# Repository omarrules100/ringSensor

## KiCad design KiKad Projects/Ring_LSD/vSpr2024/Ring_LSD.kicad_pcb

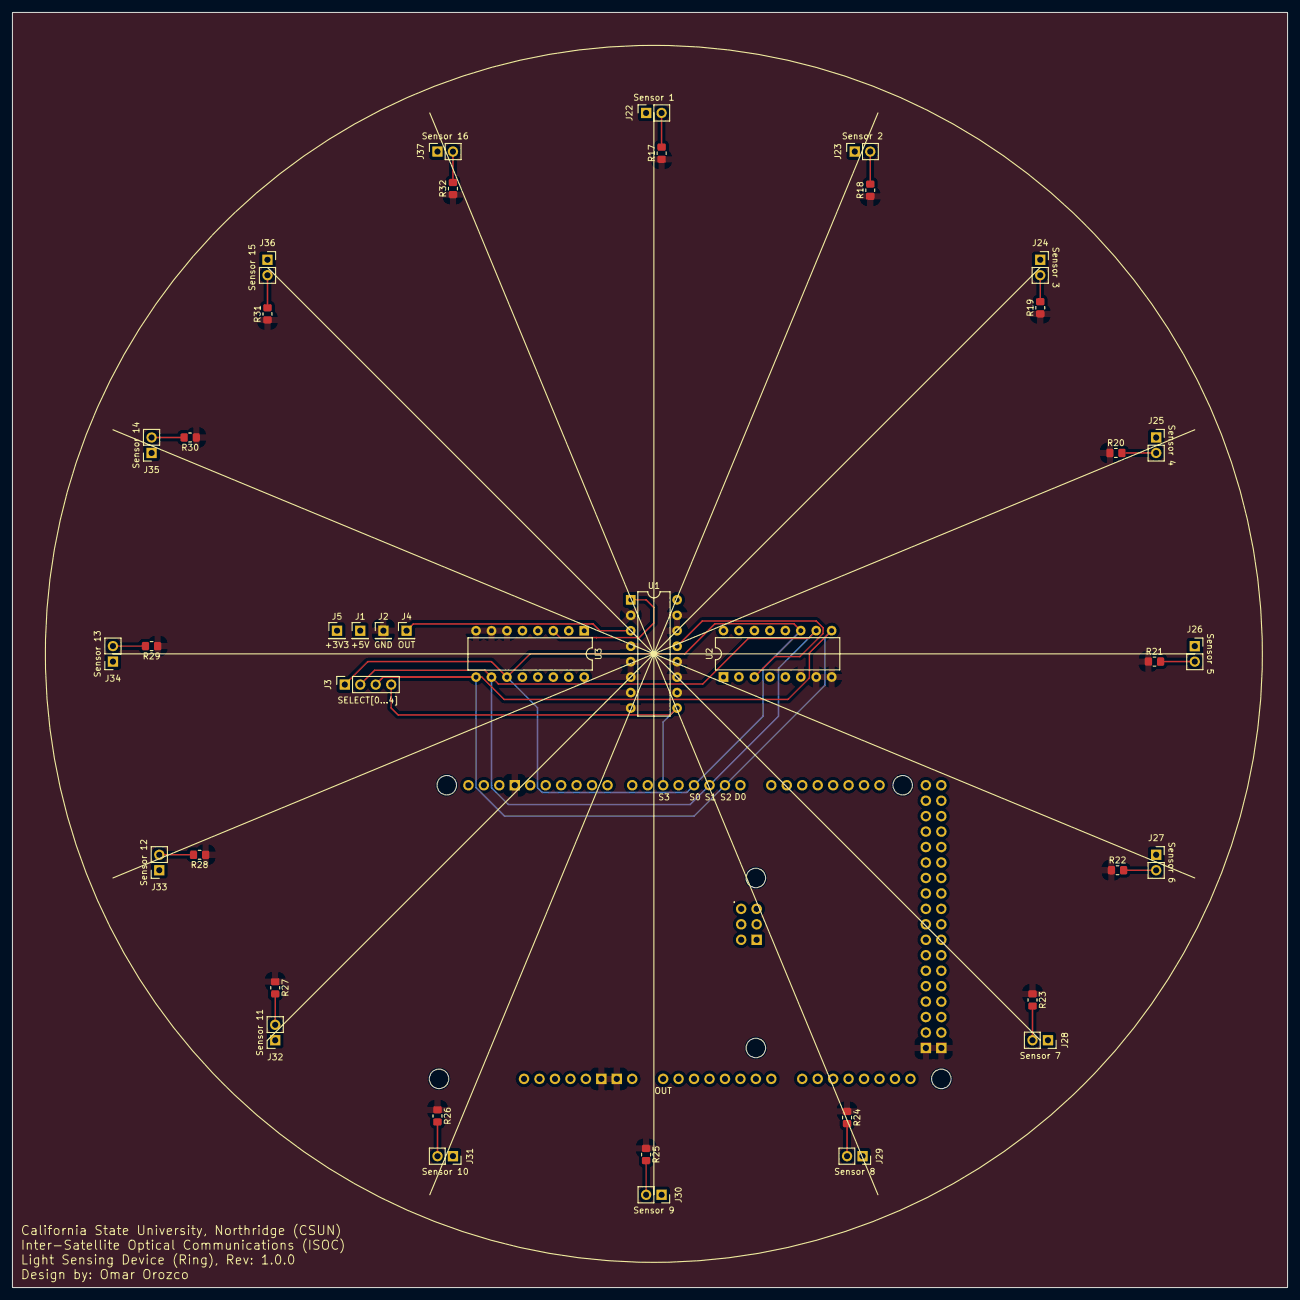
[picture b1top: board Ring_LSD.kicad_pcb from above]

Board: 4 copper layers, 209.5 x 209.5 mm, 41 parts (0 on the bottom side), 26 nets.

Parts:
A1: Arduino_Giga_R1_WiFi_Shield
J1: +5V; PinHeader_1x01_P2.54mm_Vertical
J2: GND; PinHeader_1x01_P2.54mm_Vertical
J3: SELECT[0...4]; PinSocket_1x04_P2.54mm_Vertical
J4: OUT; PinHeader_1x01_P2.54mm_Vertical
J5: +3V3; PinHeader_1x01_P2.54mm_Vertical
J22: Sensor 1; PinSocket_1x02_P2.54mm_Vertical
J23: Sensor 2; PinSocket_1x02_P2.54mm_Vertical
J24: Sensor 3; PinSocket_1x02_P2.54mm_Vertical
J25: Sensor 4; PinSocket_1x02_P2.54mm_Vertical
J26: Sensor 5; PinSocket_1x02_P2.54mm_Vertical
J27: Sensor 6; PinSocket_1x02_P2.54mm_Vertical
J28: Sensor 7; PinSocket_1x02_P2.54mm_Vertical
J29: Sensor 8; PinSocket_1x02_P2.54mm_Vertical
J30: Sensor 9; PinSocket_1x02_P2.54mm_Vertical
J31: Sensor 10; PinSocket_1x02_P2.54mm_Vertical
J32: Sensor 11; PinSocket_1x02_P2.54mm_Vertical
J33: Sensor 12; PinSocket_1x02_P2.54mm_Vertical
J34: Sensor 13; PinSocket_1x02_P2.54mm_Vertical
J35: Sensor 14; PinSocket_1x02_P2.54mm_Vertical
J36: Sensor 15; PinSocket_1x02_P2.54mm_Vertical
J37: Sensor 16; PinSocket_1x02_P2.54mm_Vertical
R17, R18, R19, R20, R21, R22, R23, R24, R25, R26, R27, R28, R29, R30, R31, R32: 5K; R_0805_2012Metric_Pad1.20x1.40mm_HandSolder
U1, U2, U3: 74HCT4051; DIP-16_W7.62mm

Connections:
+3V3: J5.1, J22.1, J23.1, J24.1, J25.1, J26.1, J27.1, J28.1, J29.1, J30.1, J31.1, J32.1, J33.1, J34.1, J35.1, J36.1, J37.1
+5V: J1.1, U1.16 (VCC), U2.16 (VCC), U3.16 (VCC)
/LSD_OUT: A1.A0, J4.1, U1.3 (Z)
/Select0: A1.D3, J3.1, U2.11 (S0), U3.11 (S0)
/Select1: A1.D2, J3.2, U2.10 (S1), U3.10 (S1)
/Select2: A1.D1 (D1/TX0), J3.3, U2.9 (S2), U3.9 (S2)
/Select3: A1.D5, J3.4, U1.9 (S2)
/Z1: U1.13 (Y0), U2.3 (Z)
/Z2: U1.1 (Y4), U3.3 (Z)
GND: A1.GND1 (GND), A1.GND2 (GND), A1.GND3 (GND), A1.GND5 (GND), A1.GND6 (GND), J2.1, R17.1, R18.1, R19.1, R20.1, R21.1, R22.1, R23.1, R24.1, R25.1, R26.1, R27.1, R28.1, R29.1, R30.1, R31.1, R32.1, U1.2 (Y6), U1.4 (Y7), U1.5 (Y5), U1.6 (~E), U1.7 (VEE), U1.8 (GND), U1.10 (S1), U1.11 (S0), U1.12 (Y3), U1.14 (Y1), U1.15 (Y2), U2.6 (~E), U2.7 (VEE), U2.8 (GND), U3.6 (~E), U3.7 (VEE), U3.8 (GND)
Sensor1: J22.2, R17.2, U2.13 (Y0)
Sensor2: J23.2, R18.2, U2.14 (Y1)
Sensor3: J24.2, R19.2, U2.15 (Y2)
Sensor4: J25.2, R20.2, U2.12 (Y3)
Sensor5: J26.2, R21.2, U2.1 (Y4)
Sensor6: J27.2, R22.2, U2.5 (Y5)
Sensor7: J28.2, R23.2, U2.2 (Y6)
Sensor8: J29.2, R24.2, U2.4 (Y7)
Sensor9: J30.2, R25.2, U3.13 (Y0)
Sensor10: J31.2, R26.2, U3.14 (Y1)
Sensor11: J32.2, R27.2, U3.15 (Y2)
Sensor12: J33.2, R28.2, U3.12 (Y3)
Sensor13: J34.2, R29.2, U3.1 (Y4)
Sensor14: J35.2, R30.2, U3.5 (Y5)
Sensor15: J36.2, R31.2, U3.2 (Y6)
Sensor16: J37.2, R32.2, U3.4 (Y7)

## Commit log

2024-04-16 Add files via upload
    current ring sensor iteration
2024-09-08 Add files via upload
    PCB Design based on Spring 2024 breadboard design
2024-09-08 Organization of project files and directories
